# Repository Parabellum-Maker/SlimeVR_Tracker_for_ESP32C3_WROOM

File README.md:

[Slimme VR Tracker for ESP32](https://github.com/SlimeVR/SlimeVR-Tracker-ESP)を使用する自作トラッカー基板のデータです。\
トラッカー基板上に保護回路などないため、使用する場合は注意が必要です。\
基板に関して、性能評価や動作安定性、安全性(EMC試験など)の評価は実施していないことに留意ください。

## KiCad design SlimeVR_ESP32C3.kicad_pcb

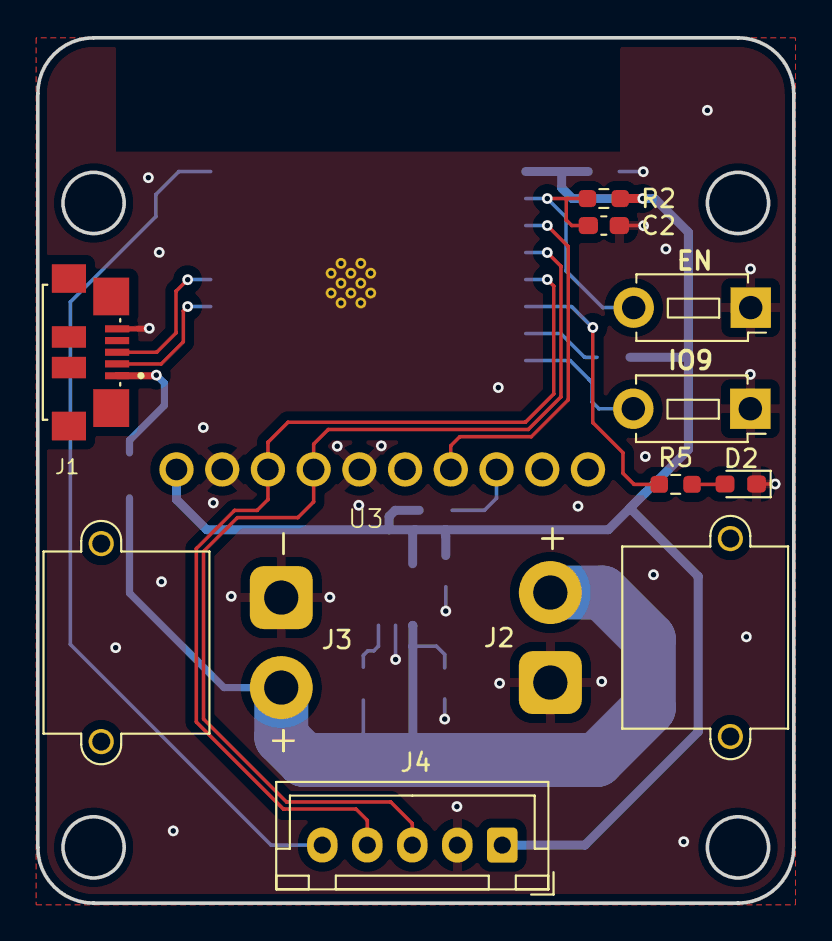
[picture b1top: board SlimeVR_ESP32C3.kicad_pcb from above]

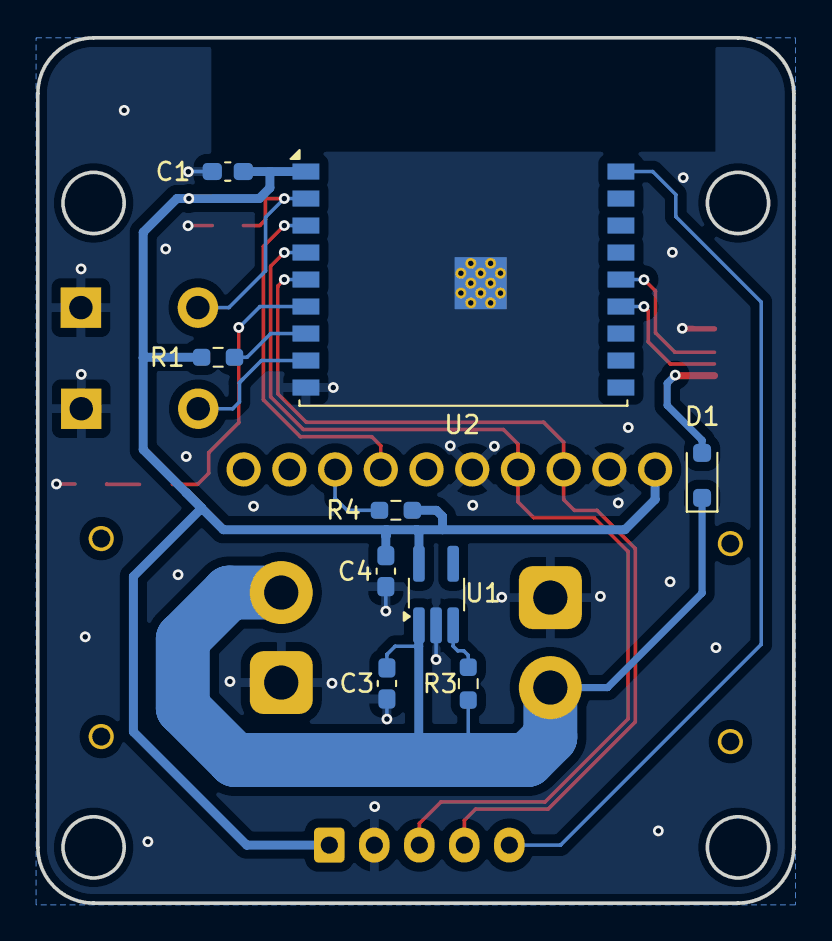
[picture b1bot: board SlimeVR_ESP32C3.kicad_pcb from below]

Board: 2 copper layers, 42.0 x 48.1 mm, 20 parts (9 on the bottom side), 17 nets.

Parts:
C1, C2, C4: 10u; C_0603_1608Metric_Pad1.08x0.95mm_HandSolder
C3: 1u; C_0603_1608Metric_Pad1.08x0.95mm_HandSolder
D1: D; D_SOD-323_HandSoldering
D2: LED; LED_0603_1608Metric_Pad1.05x0.95mm_HandSolder
J1: ZX62R-B-5P_30_; HRS_ZX62R-B-5P_30_
J2, J3: Conn_01x02_Pin; AMASS_XT30PW-M_1x02_P2.50mm_Horizontal
J4: Conn_01x05_Pin; JST_XH_B5B-XH-A_1x05_P2.50mm_Vertical
R1, R2, R3, R4, R5: 10k; R_0603_1608Metric_Pad0.98x0.95mm_HandSolder
SW1, SW2: SW_Push; SW_PUSH_1P1T_6x3.5mm_H4.3_APEM_MJTP1243
U1: RT9080-33GJ5; TSOT-23-5_HandSoldering
U2: ESP32-C3-WROOM-02
U3: BNO085; BNO08X

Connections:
+3V3: C1.1, C4.1, J4.1, R1.1, R2.1, R4.1, U1.5 (VOUT), U2.1 (3V3), U3.1 (VCC)
+5V: D1.2 (A), J1.1 (VUSB)
/D+: J1.3 (D+), U2.14 (IO19)
/D-: J1.2 (D-), U2.13 (IO18)
/INT0: U2.3 (IO4), U3.7 (INT)
/INT1: J4.5, U2.18 (IO0)
/LED: R5.1, U2.6 (IO7)
/SCL: J4.4, U2.5 (IO6), U3.3 (SCL)
/SDA: J4.3, U2.4 (IO5), U3.4 (SDA)
GND: C1.2, C2.2, C3.2, C4.2, D2.1 (K), J1.5 (GND), J2.1, J3.1, J4.2, SW1.1, SW2.1, U1.2 (GND), U2.9 (GND), U2.19 (GND), U3.2 (GND), U3.5 (ADD)
unnamed: D2.2 (A), R5.2
unnamed: R3.2, U1.3 (EN)
unnamed: C2.1, R2.2, SW2.2, U2.2 (EN)
unnamed: R1.2, U2.7 (IO8)
unnamed: SW1.2, U2.8 (IO9)
unnamed: R4.2, U3.8 (RST)
VCC: C3.1, D1.1 (K), J2.2, J3.2, R3.1, U1.1 (VIN)

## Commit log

2025-08-15 Add files
